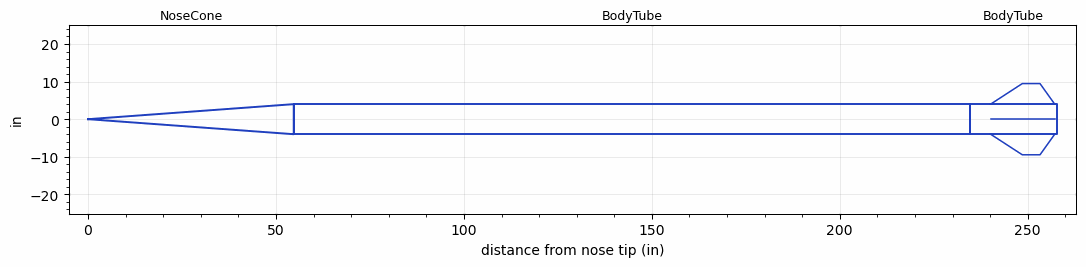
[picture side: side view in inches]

<RASAeroDocument>
 <FileVersion>2</FileVersion>
 <RocketDesign>
  <NoseCone>
   <Length>54.7243</Length>
   <Diameter>8</Diameter>
   <Shape>Conical</Shape>
   <Location>0</Location>
  </NoseCone>
  <BodyTube>
   <Length>179.9996</Length>
   <Diameter>8</Diameter>
   <Location>54.7243</Location>
  </BodyTube>
  <BodyTube>
   <Length>23</Length>
   <Diameter>8</Diameter>
   <Location>234.7239</Location>
   <Fin>
    <Count>4</Count>
    <Chord>17.0472</Chord>
    <Span>5.4724</Span>
    <SweepDistance>8.4252</SweepDistance>
    <TipChord>4.7106</TipChord>
    <Thickness>0.25</Thickness>
    <Location>17.5984</Location>
    <AirfoilSection>Square</AirfoilSection>
   </Fin>
  </BodyTube>
  <Surface>Rough Camouflage Paint</Surface>
  <CD>0</CD>
  <ModifiedBarrowman>False</ModifiedBarrowman>
  <Turbulence>False</Turbulence>
  <UseBooster1>False</UseBooster1>
  <UseBooster2>False</UseBooster2>
  <Comments>Testing for stability --&gt; upthrust sim</Comments>
 </RocketDesign>
 <LaunchSite>
  <Altitude>0</Altitude>
  <Pressure>29.9214</Pressure>
  <RodAngle>0</RodAngle>
  <RodLength>3.2808</RodLength>
  <Temperature>59</Temperature>
  <WindSpeed>4.4739</WindSpeed>
 </LaunchSite>
 <Recovery>
  <Altitude1>0</Altitude1>
  <Altitude2>0</Altitude2>
  <DeviceType1>None</DeviceType1>
  <DeviceType2>None</DeviceType2>
  <Event1>False</Event1>
  <Event2>False</Event2>
  <Size1>0</Size1>
  <Size2>0</Size2>
  <EventType1>None</EventType1>
  <EventType2>None</EventType2>
  <CD1>0</CD1>
  <CD2>0</CD2>
 </Recovery>
 <SimulationList>
  <Simulation>
   <SustainerLaunchWt>121.9733</SustainerLaunchWt>
   <SustainerCG>155.6656</SustainerCG>
   <SustainerIgnitionDelay>0</SustainerIgnitionDelay>
   <Booster1SeparationDelay>0</Booster1SeparationDelay>
   <Booster1IgnitionDelay>0</Booster1IgnitionDelay>
   <IncludeBooster1>False</IncludeBooster1>
   <Booster2Delay>0</Booster2Delay>
   <IncludeBooster2>False</IncludeBooster2>
  </Simulation>
 </SimulationList>
</RASAeroDocument>
